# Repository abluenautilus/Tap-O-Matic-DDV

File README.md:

# Tap-O-Matic DDV

The Olivia Artz Modular Time Machine, version by Harry Richardson, modified by Blue Nautilus and the DivKid Discord, and finally tweaked heavily by Eris Fairbanks. We've come full circle folks!

This version modifies the [Tap-O-Matic version](https://github.com/cormallen/tap-o-matic) by HR in two ways:
<ul>
<li>It moves the pan pots down by 2mm. This makes the build much easier since the pan pots don't butt up against the sliders.</li>
<li>It moves the power header on the back so that it doesn't interfere with one of the jacks. This means you don't have to shave plastic off the jack.</li>
</ul>

**Eris's Software Notes:**
- Read heads are paired in order to utilize the PSRAM cache more effectively.
- The dynamics management system is drastically improved, utilizing a 4-point lookahead system per read-head pair.
- Filters used to be one-poles, now they're my own SVF implementation. Steeper cutoff, more resonance, more character.
- Code is a bit more readable and cleaner I think, constants and twiddle factors gathered up and commented.
- CPU usage is better, though extreme time variation might still cause frame drops? I haven't seen any, but that doesn't mean they aren't possible. Might be good to bump block size up to 8 if we notice any.
- Feedback can still distort. Dynamic range still isn't what I'd like it to be and probably never will be unless there's a hardware change to support 20vpp.

## Front Panel

All of the files for producing the panels are in the panel folder. This panel was fabricated by http://pcbway.com. It's a PCB panel using matte black solder mask:

## BOM

Our modified BOM is here:
https://docs.google.com/spreadsheets/d/1hPb3Es_wUxIoNBYNVZt8cKr9BfJMghtDLR-cnE-fVQ0/edit?gid=118381065#gid=118381065

## Fabrication Instructions

The fabrication guide can be found here: 

https://docs.google.com/document/d/1D_RPgzVUW2ujZSJS9yKFKmFV2mPIwQp9BS7iKvg6IVI/edit?tab=t.0

## Build Instructions

The build guide can be found here: 

https://docs.google.com/document/d/1rPKsOXEx5abdQNxCypnp2nViSWlIubEysEng-fZd7tw/edit?tab=t.0

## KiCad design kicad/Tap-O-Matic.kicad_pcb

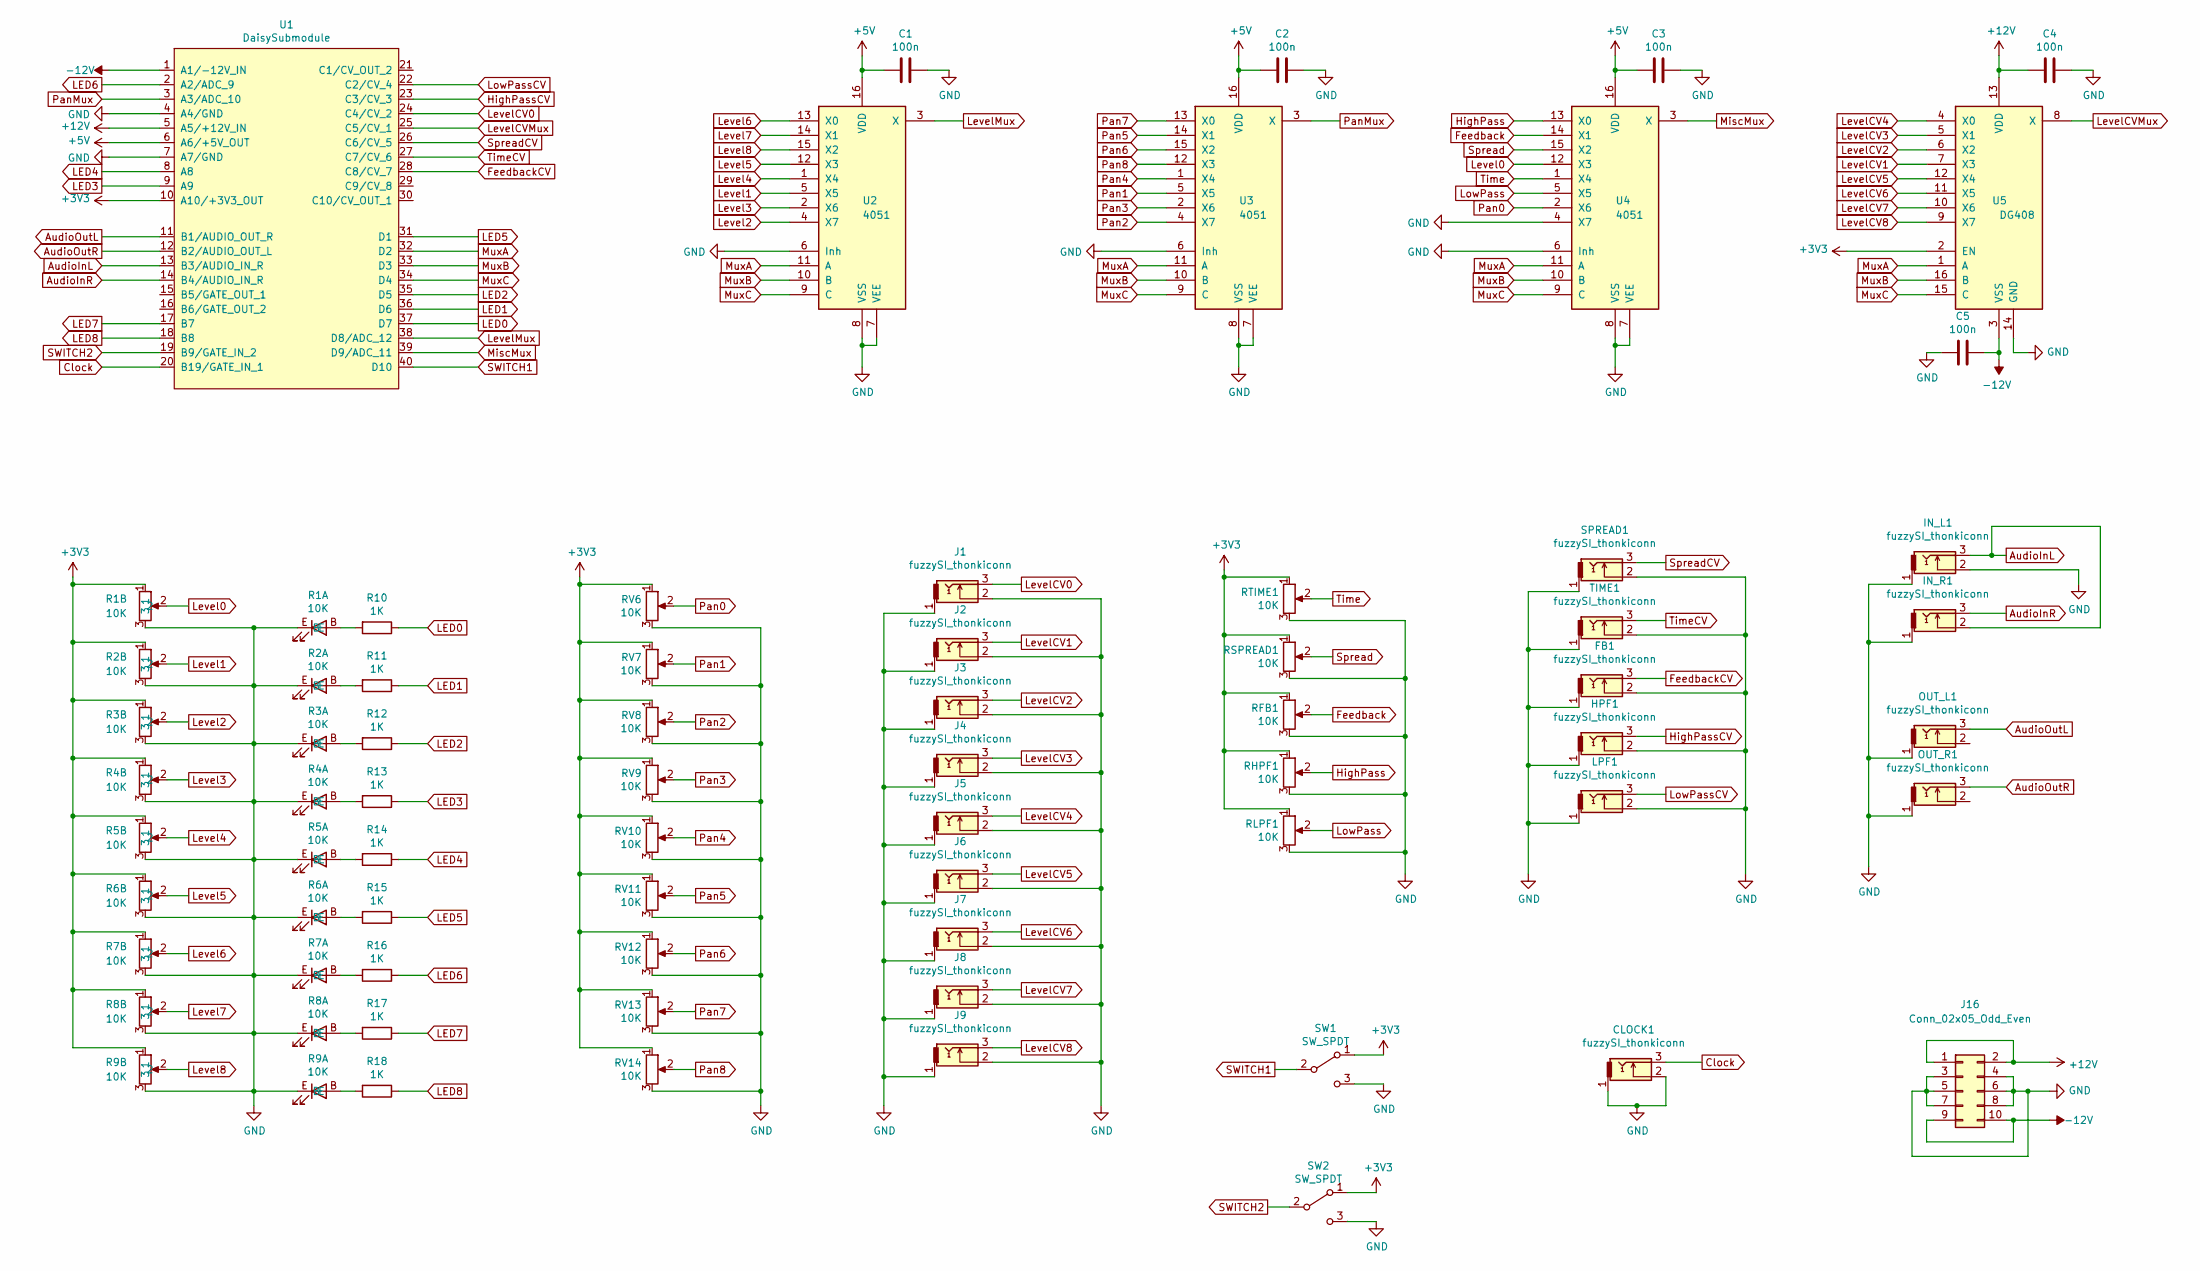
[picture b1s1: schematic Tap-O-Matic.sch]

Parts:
C1, C2, C3, C4, C5: 100n; C_Disc_D3.8mm_W2.6mm_P2.50mm
CLOCK1: fuzzySI_thonkiconn; thonkiconn_fuzzySi
FB1: fuzzySI_thonkiconn; thonkiconn_fuzzySi
HPF1: fuzzySI_thonkiconn; thonkiconn_fuzzySi
IN_L1: fuzzySI_thonkiconn; thonkiconn_fuzzySi
IN_R1: fuzzySI_thonkiconn; thonkiconn_fuzzySi
J1, J2, J3, J4, J5, J6, J7, J8, J9: fuzzySI_thonkiconn; thonkiconn_fuzzySi
J16: Conn_02x05_Odd_Even; PinHeader_2x05_P2.54mm_Vertical
LPF1: fuzzySI_thonkiconn; thonkiconn_fuzzySi
OUT_L1: fuzzySI_thonkiconn; thonkiconn_fuzzySi
OUT_R1: fuzzySI_thonkiconn; thonkiconn_fuzzySi
R1, R2, R3, R4, R5, R6, R7, R8, R9: 10K; PTL45
R10, R11, R12, R13, R14, R15, R16, R17, R18: 1K; R_Axial_DIN0207_L6.3mm_D2.5mm_P7.62mm_Horizontal
RFB1: 10K; Potentiometer_Alpha_RD901F-40-00D_Single_Vertical
RHPF1: 10K; Potentiometer_Alpha_RD901F-40-00D_Single_Vertical
RLPF1: 10K; Potentiometer_Alpha_RD901F-40-00D_Single_Vertical
RSPREAD1: 10K; Potentiometer_Alpha_RD901F-40-00D_Single_Vertical
RTIME1: 10K; Potentiometer_Alpha_RD901F-40-00D_Single_Vertical
RV6, RV7, RV8, RV9, RV10, RV11, RV12, RV13, RV14: 10K; SongHuei_tall_trimmer
SPREAD1: fuzzySI_thonkiconn; thonkiconn_fuzzySi
SW1, SW2: SW_SPDT; SALECOM_ES4-2_SPDT
TIME1: fuzzySI_thonkiconn; thonkiconn_fuzzySi
U1: DaisySubmodule
U2, U3, U4: 4051; DIP-16_W7.62mm_Socket
U5: DG408; DIP-16_W7.62mm_Socket

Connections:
+3V3: R1.1, R2.1, R3.1, R4.1, R5.1, R6.1, R7.1, R8.1, R9.1, RFB1.1, RHPF1.1, RLPF1.1, RSPREAD1.1, RTIME1.1, RV6.1, RV7.1, RV8.1, RV9.1, RV10.1, RV11.1, RV12.1, RV13.1, RV14.1, SW1.1 (A), SW2.1 (A), U1.10 (A10/+3V3_OUT), U5.2 (EN)
+5V: C1.2, C2.2, C3.2, U1.6 (A6/+5V_OUT), U2.16 (VDD), U3.16 (VDD), U4.16 (VDD)
+12V: C4.2, J16.1, J16.2, U1.5 (A5/+12V_IN), U5.13 (VDD)
-12V: C5.1, J16.9, J16.10, U1.1 (A1/-12V_IN), U5.3 (VSS)
AudioInL: IN_L1.3, IN_R1.2, U1.13 (B3/AUDIO_IN_R)
AudioInR: IN_R1.3, U1.14 (B4/AUDIO_IN_R)
AudioOutL: OUT_L1.3, U1.11 (B1/AUDIO_OUT_R)
AudioOutR: OUT_R1.3, U1.12 (B2/AUDIO_OUT_L)
Clock: CLOCK1.3, U1.20 (B19/GATE_IN_1)
Feedback: RFB1.2, U4.14 (X1)
FeedbackCV: FB1.3, U1.28 (C8/CV_7)
GND: C1.1, C2.1, C3.1, C4.1, C5.2, CLOCK1.1, CLOCK1.2, FB1.1, FB1.2, HPF1.1, HPF1.2, IN_L1.1, IN_L1.2, IN_R1.1, J1.1, J1.2, J2.1, J2.2, J3.1, J3.2, J4.1, J4.2, J5.1, J5.2, J6.1, J6.2, J7.1, J7.2, J8.1, J8.2, J9.1, J9.2, J16.3, J16.4, J16.5, J16.6, J16.7, J16.8, LPF1.1, LPF1.2, OUT_L1.1, OUT_R1.1, R1.3, R1.E, R2.3, R2.E, R3.3, R3.E, R4.3, R4.E, R5.3, R5.E, R6.3, R6.E, R7.3, R7.E, R8.3, R8.E, R9.3, R9.E, RFB1.3, RHPF1.3, RLPF1.3, RSPREAD1.3, RTIME1.3, RV6.3, RV7.3, RV8.3, RV9.3, RV10.3, RV11.3, RV12.3, RV13.3, RV14.3, SPREAD1.1, SPREAD1.2, SW1.3 (C), SW2.3 (C), TIME1.1, TIME1.2, U1.4 (A4/GND), U1.7 (A7/GND), U2.6 (Inh), U2.7 (VEE), U2.8 (VSS), U3.6 (Inh), U3.7 (VEE), U3.8 (VSS), U4.4 (X7), U4.6 (Inh), U4.7 (VEE), U4.8 (VSS), U5.14 (GND)
HighPass: RHPF1.2, U4.13 (X0)
HighPassCV: HPF1.3, U1.23 (C3/CV_3)
LED0: R10.1, U1.37 (D7)
LED1: R11.1, U1.36 (D6)
LED2: R12.1, U1.35 (D5)
LED3: R13.1, U1.9 (A9)
LED4: R14.1, U1.8 (A8)
LED5: R15.1, U1.31 (D1)
LED6: R16.1, U1.2 (A2/ADC_9)
LED7: R17.1, U1.17 (B7)
LED8: R18.1, U1.18 (B8)
Level0: R1.2, U4.12 (X3)
Level1: R2.2, U2.5 (X5)
Level2: R3.2, U2.4 (X7)
Level3: R4.2, U2.2 (X6)
Level4: R5.2, U2.1 (X4)
Level5: R6.2, U2.12 (X3)
Level6: R7.2, U2.13 (X0)
Level7: R8.2, U2.14 (X1)
Level8: R9.2, U2.15 (X2)
LevelCV0: J1.3, U1.24 (C4/CV_2)
LevelCV1: J2.3, U5.7 (X3)
LevelCV2: J3.3, U5.6 (X2)
LevelCV3: J4.3, U5.5 (X1)
LevelCV4: J5.3, U5.4 (X0)
LevelCV5: J6.3, U5.12 (X4)
LevelCV6: J7.3, U5.11 (X5)
LevelCV7: J8.3, U5.10 (X6)
LevelCV8: J9.3, U5.9 (X7)
LevelCVMux: U1.25 (C5/CV_1), U5.8 (X)
LevelMux: U1.38 (D8/ADC_12), U2.3 (X)
LowPass: RLPF1.2, U4.5 (X5)
LowPassCV: LPF1.3, U1.22 (C2/CV_4)
MiscMux: U1.39 (D9/ADC_11), U4.3 (X)
MuxA: U1.32 (D2), U2.11 (A), U3.11 (A), U4.11 (A), U5.1 (A)
MuxB: U1.33 (D3), U2.10 (B), U3.10 (B), U4.10 (B), U5.16 (B)
MuxC: U1.34 (D4), U2.9 (C), U3.9 (C), U4.9 (C), U5.15 (C)
unnamed: R1.B, R10.2
unnamed: R2.B, R11.2
unnamed: R3.B, R12.2
unnamed: R4.B, R13.2
unnamed: R5.B, R14.2
unnamed: R6.B, R15.2
unnamed: R7.B, R16.2
unnamed: R8.B, R17.2
unnamed: R9.B, R18.2
Pan0: RV6.2, U4.2 (X6)
Pan1: RV7.2, U3.5 (X5)
Pan2: RV8.2, U3.4 (X7)
Pan3: RV9.2, U3.2 (X6)
Pan4: RV10.2, U3.1 (X4)
Pan5: RV11.2, U3.14 (X1)
Pan6: RV12.2, U3.15 (X2)
Pan7: RV13.2, U3.13 (X0)
Pan8: RV14.2, U3.12 (X3)
PanMux: U1.3 (A3/ADC_10), U3.3 (X)
SWITCH1: SW1.2 (B), U1.40 (D10)
SWITCH2: SW2.2 (B), U1.19 (B9/GATE_IN_2)
Spread: RSPREAD1.2, U4.15 (X2)
SpreadCV: SPREAD1.3, U1.26 (C6/CV_5)
Time: RTIME1.2, U4.1 (X4)
TimeCV: TIME1.3, U1.27 (C7/CV_6)

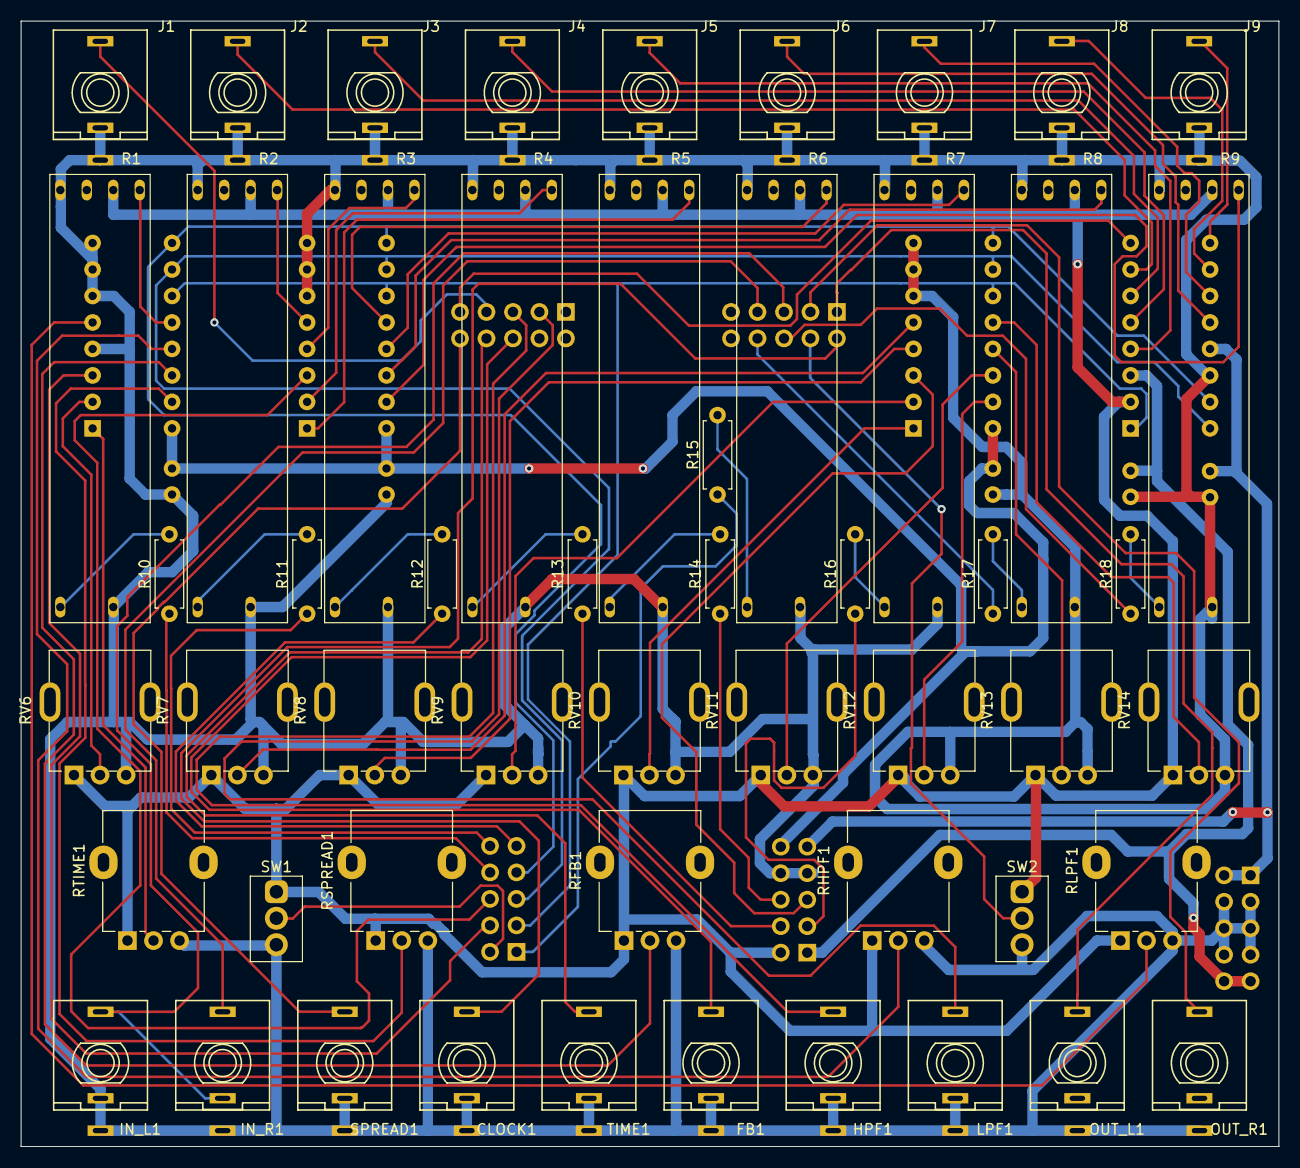
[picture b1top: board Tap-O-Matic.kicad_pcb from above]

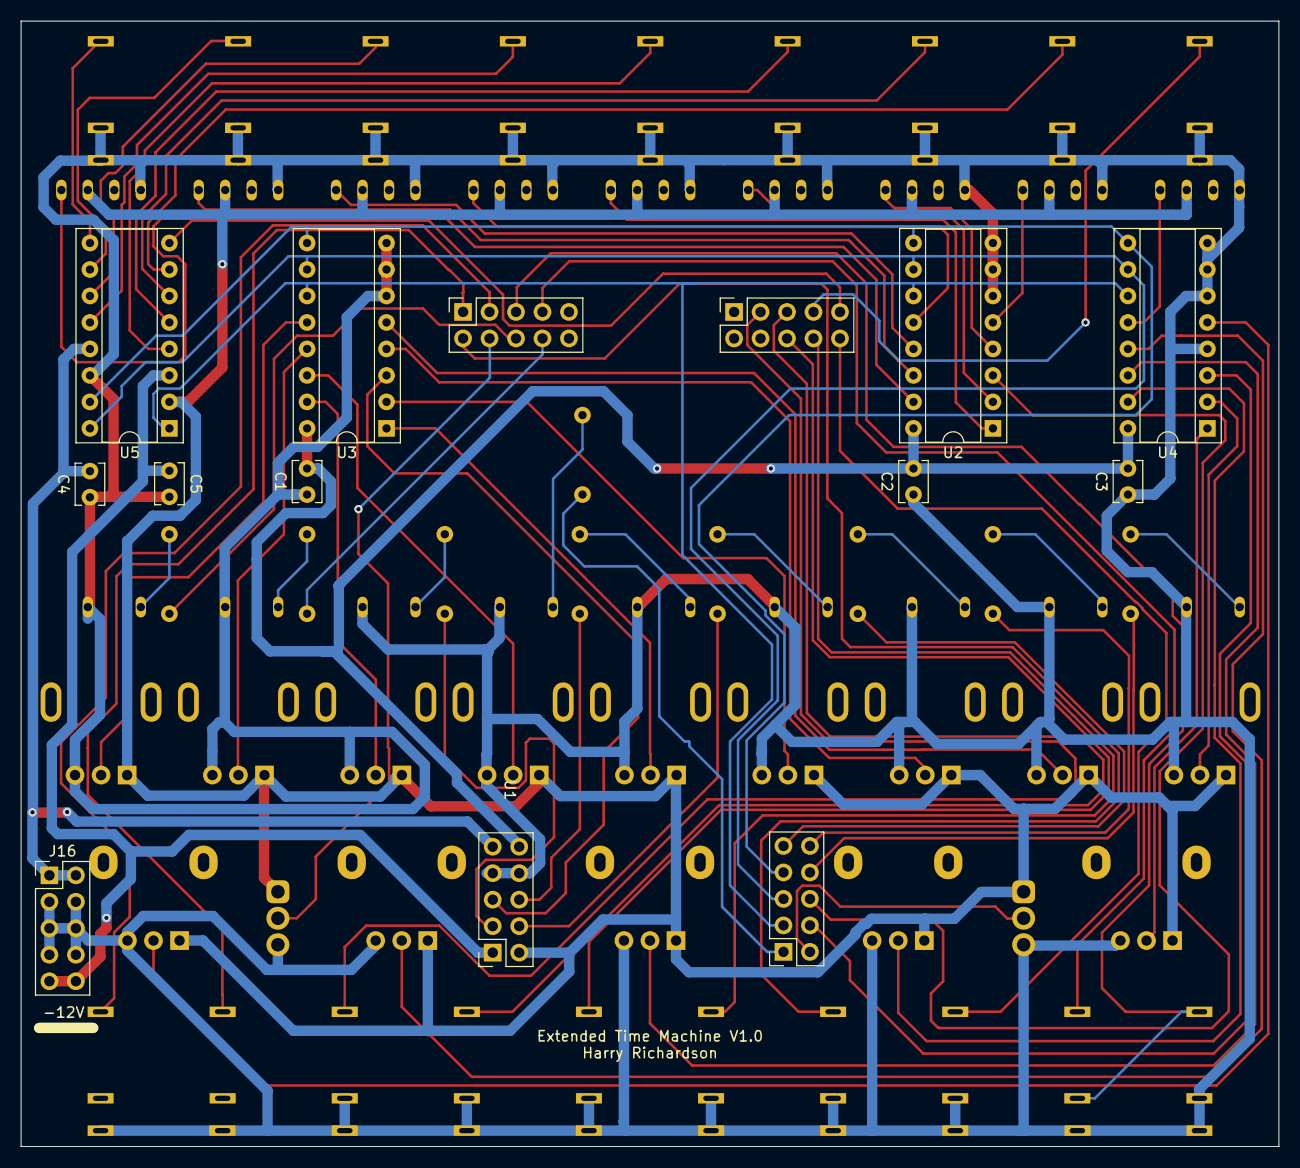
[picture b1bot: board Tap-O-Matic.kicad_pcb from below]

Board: 2 copper layers, 120.7 x 108.0 mm, 64 parts (11 on the bottom side), 74 nets.

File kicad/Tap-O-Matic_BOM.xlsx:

Id | Designator | Footprint | Quantity | Designation | Part# | Link | Price/Ea | TotalPrice
1 | R6,R7,R1,R9,R8,R5,R4,R3,R2 | PTL45 | 9 | 10K | PTL30-15R0-104B2 | https://www.mouser.com/ProductDetail/Bourns/PTL30-15R0-104B2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 | 1.87 | 16.830000000000002
2 | RV7,RV14,RV13,RV12,RV11,RV10,RV9,RV8,RV6 | SongHuei_tall_trimmer | 9 | 10K |  | https://www.thonk.co.uk/shop/ttpots/ | 1.22 | 10.98
3 | SW2,SW1 | SALECOM_ES4-2_SPDT | 2 | SW_SPDT |  | https://www.thonk.co.uk/shop/ttpots/ | 1.84 | 3.68
4 | U1 | DaisySubmodule | 1 | DaisySubmodule |  | https://electro-smith.com/products/patch-submodule | 24 | 24
5 | RSPREAD1,RLPF1,RHPF1,RFB1,RTIME1 | Potentiometer_Alpha_RD901F-40-00D_Single_Vertical | 5 | 10K |  | https://www.thonk.co.uk/shop/alpha-9mm-pots/ | 2.15 | 10.75
6 | C5,C4,C3,C2,C1 | C_Disc_D3.8mm_W2.6mm_P2.50mm | 5 | 100n |  |  |  | 0
7 | J16 | PinHeader_2x05_P2.54mm_Vertical | 1 | Conn_02x05_Odd_Even |  |  |  | 0
8 | U5 | DIP-16_W7.62mm_Socket | 1 | DG408 |  |  |  | 0
9 | U4,U3,U2 | DIP-16_W7.62mm_Socket | 3 | 4051 |  |  |  | 0
10 | R18,R17,R16,R15,R14,R13,R12,R11,R10 | R_Axial_DIN0207_L6.3mm_D2.5mm_P7.62mm_Horizontal | 9 | 1K |  |  |  | 0
11 | OUT_R1,OUT_L1,IN_R1,IN_L1,LPF1,HPF1,FB1,TIME1,SPREAD1,CLOCK1,J9,J8,J7,J6,J5,J4,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 | thonkiconn_fuzzySi | 19 | fuzzySI_thonkiconn |  |  |  | 0
12 | U2, U3, U4, U6 | DIP-16_W7.62mm_Socket | 4 | 16-pin DIP sockets |  |  |  | 0
13 | U1 | 2x5 header | 4 | 2x5 headers |  |  |  | 0
Total |  |  |  |  |  |  |  | 66.240000000000009

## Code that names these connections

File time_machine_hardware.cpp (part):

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                FLT_VAR(5, panKnobNoise_[i].GetRange()));
        }

        const char* cvNames[] = {"Spread", "Time", "Feedback", "Highpass", "Lowpass", "LevelDry"};
        PrintLine("CVs:");
        for (int i = 0; i < 6; i++)
        {
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
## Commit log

2025-04-14 readme
2025-04-14 small changes
2025-04-23 full changes for second iteration
2025-05-04 updaing for new libdaisy
2025-05-04 working version
2025-05-05 typo
2025-05-08 Build guide addition
2025-05-21 various updates
2025-05-21 readme updates
2025-05-21 readme typo
2025-05-21 removing unused libraries
2025-05-22 added fabrication guide
2025-05-27 adding text to back mask layer
2025-05-29 centered text on front panel
2025-05-29 more text fixes
2025-06-19 updated REAMDE
2025-07-10 gitignore
2025-07-10 adds pan to dry signal
2025-07-10 cleanup
2025-07-15 changing number of samples per block
2026-03-22 Code cleanup, messed with calibration (probably need testing), added lookahead dynamics management, tied read heads together to improve PSRAM cache performance, fixed panning so that it doesn't mess 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
2026-03-24 Attempting to further reduce noise and optimize CPU usage by doing some faster math, moving LED handling to while loop.
2026-03-24 Remove that first tap. Was creating unncessary cache hits.
